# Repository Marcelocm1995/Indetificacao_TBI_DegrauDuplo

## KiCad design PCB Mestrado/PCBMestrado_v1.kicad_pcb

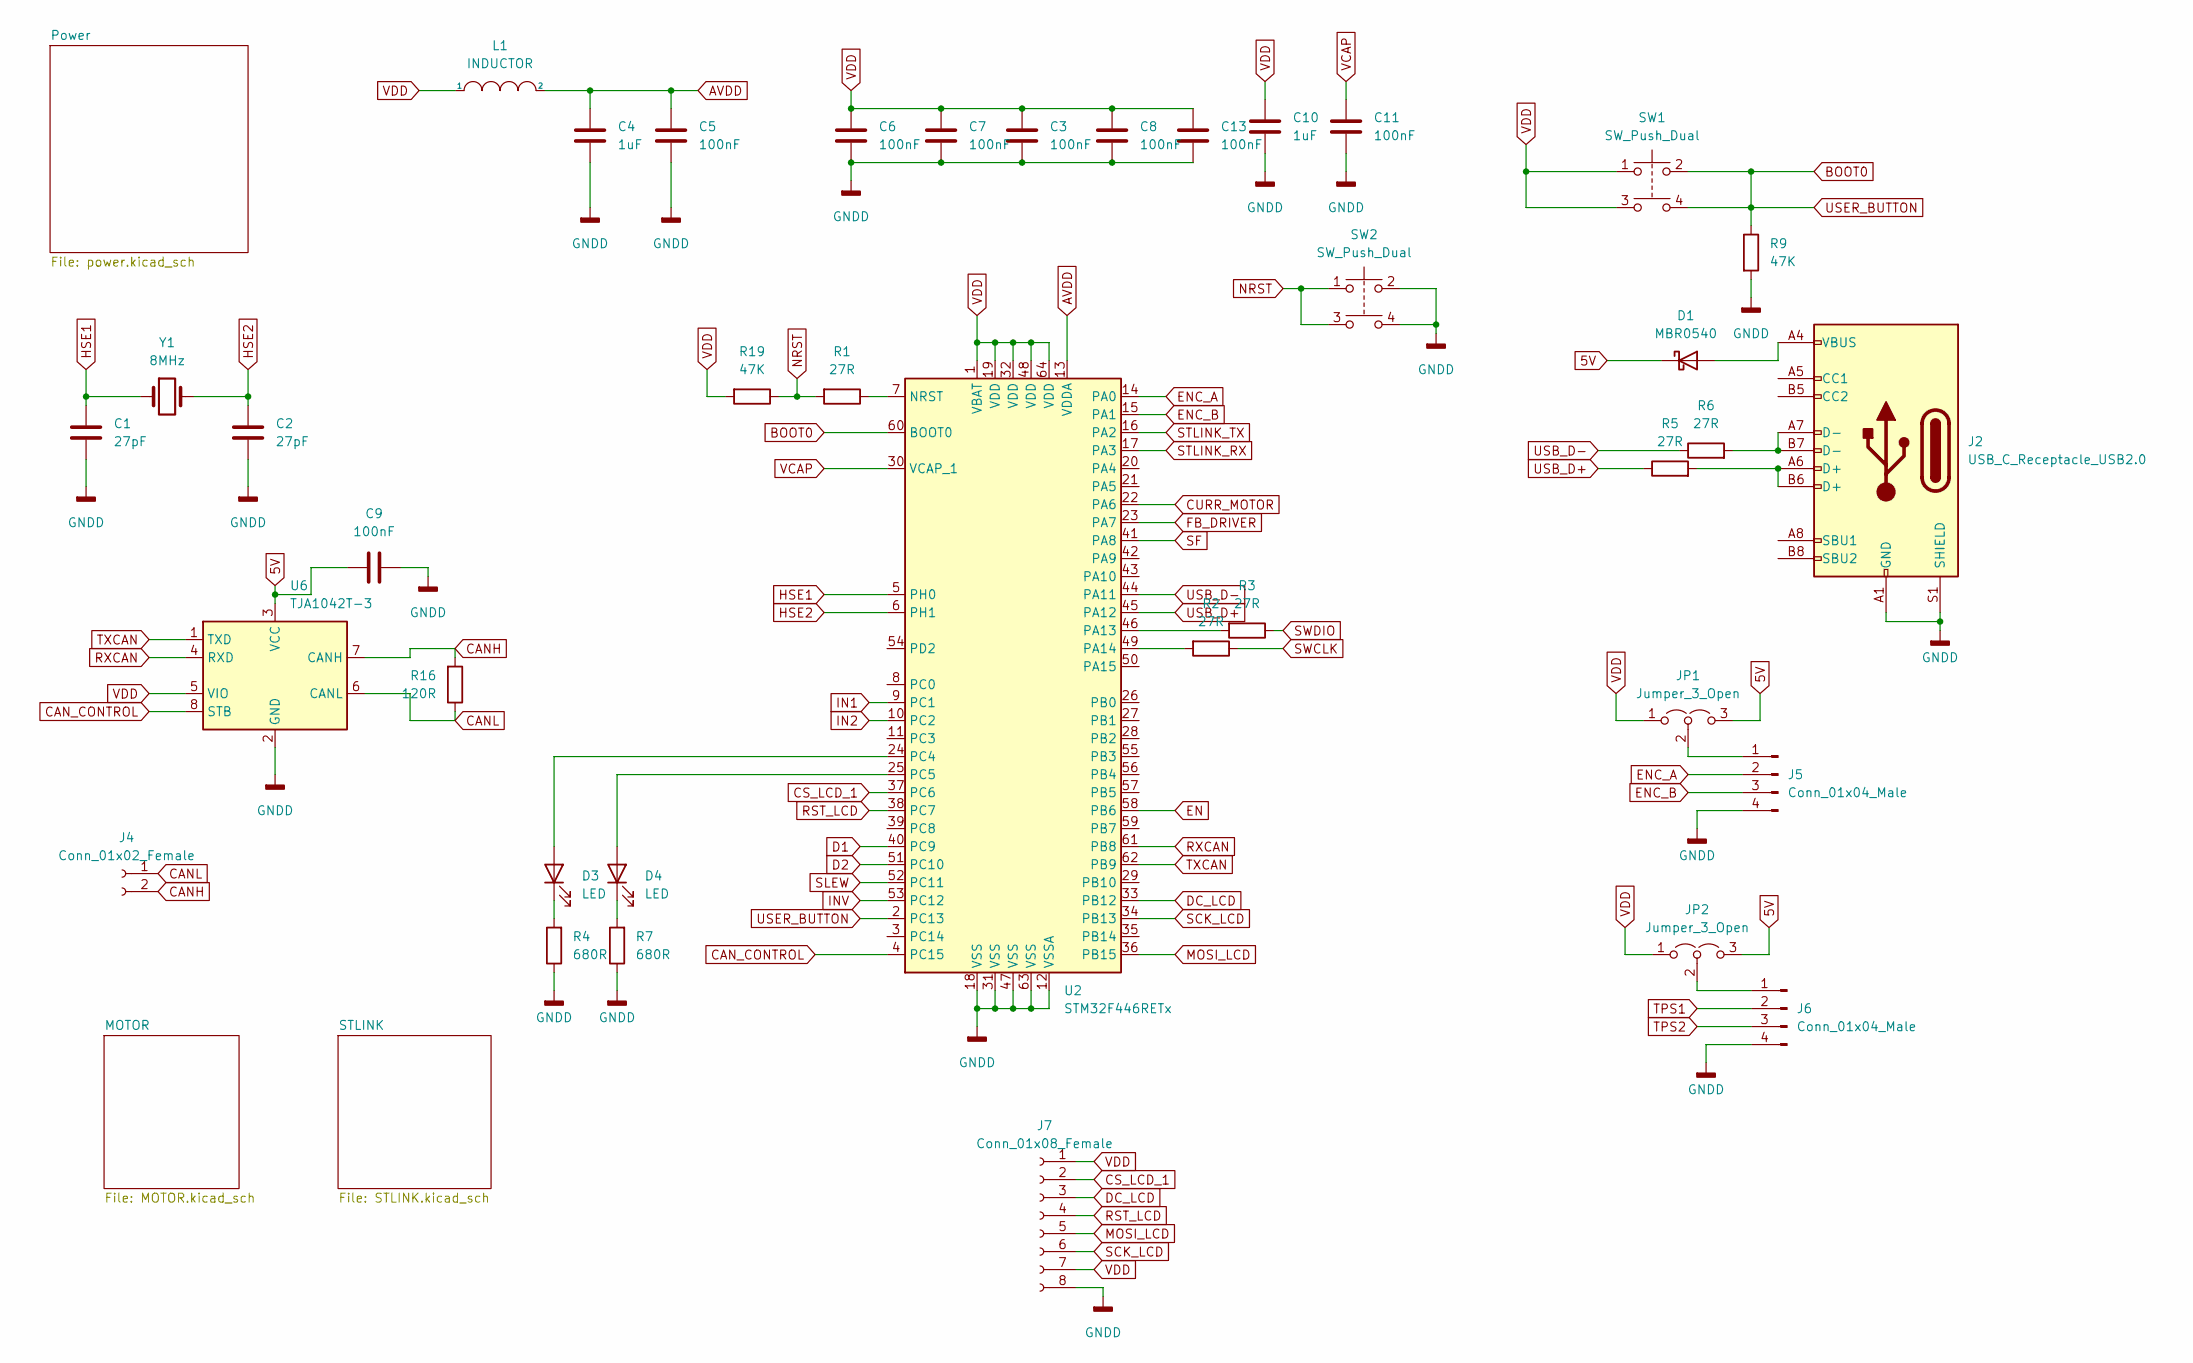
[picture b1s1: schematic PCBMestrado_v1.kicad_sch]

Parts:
C1, C2: 27pF; C_0603_1608Metric; LCSC Part C1653
C3, C5, C6, C7, C8, C9, C11, C13: 100nF; C_0603_1608Metric; LCSC Part C14663
C4, C10: 1uF; C_1206_3216Metric; LCSC Part C1848
D1: MBR0540; D_SOD-123; LCSC Part C699113
D3, D4: LED; LED_0603_1608Metric
J2: USB_C_Receptacle_USB2.0; USB_C_Receptacle_HRO_TYPE-C-31-M-12
J4: Conn_01x02_Female; PhoenixContact_MSTBA_2,5_2-G-5,08_1x02_P5.08mm_Horizontal
J5, J6: Conn_01x04_Male; JST_EH_B4B-EH-A_1x04_P2.50mm_Vertical
J7: Conn_01x08_Female; JST_EH_B8B-EH-A_1x08_P2.50mm_Vertical
JP1, JP2: Jumper_3_Open; SolderJumper-3_P2.0mm_Open_TrianglePad1.0x1.5mm
L1: INDUCTOR; L_0603_1608Metric; LCSC Part C2907080
R1, R2, R3: 27R; R_0603_1608Metric; LCSC Part C25819
R4, R7: 680R; R_0603_1608Metric; LCSC Part C25190
R5, R6: 27R; R_0603_1608Metric; LCSC Part C25190
R9, R19: 47K; R_0603_1608Metric; LCSC Part C25819
R16: 120R; R_0603_1608Metric
SW1, SW2: SW_Push_Dual; SW_SPST_TL3342
U2: STM32F446RETx; LQFP-64_10x10mm_P0.5mm
U6: TJA1042T-3; SOIC-8_3.9x4.9mm_P1.27mm
Y1: 8MHz; Crystal_SMD_3225-4Pin_3.2x2.5mm; LCSC Part C518154

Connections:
5V: C9.1, D1.1 (K), JP1.3 (B), JP2.3 (B), U6.3 (VCC); also elsewhere on the board
AVDD: C4.1, C5.1, L1.2, U2.13 (VDDA)
BOOT0: R9.1, SW1.2, SW1.4, U2.2 (PC13), U2.60 (BOOT0)
CANH: J4.2, R16.2, U6.7 (CANH)
CANL: J4.1, R16.1, U6.6 (CANL)
CAN_CONTROL: U2.4 (PC15), U6.8 (STB)
CS_LCD_1: J7.2, U2.37 (PC6)
CURR_MOTOR: U2.22 (PA6); also elsewhere on the board
D1: U2.40 (PC9); also elsewhere on the board
D2: U2.51 (PC10); also elsewhere on the board
DC_LCD: J7.3, U2.33 (PB12)
EN: U2.58 (PB6); also elsewhere on the board
ENC_A: J5.2, U2.14 (PA0)
ENC_B: J5.3, U2.15 (PA1)
FB_DRIVER: U2.23 (PA7); also elsewhere on the board
GNDD: C1.2, C2.2, C3.2, C4.2, C5.2, C6.2, C7.2, C8.2, C9.2, C10.2, C11.2, C13.2, J2.A1 (GND), J2.A12 (GND), J2.B1 (GND), J2.B12 (GND), J2.S1 (SHIELD), J5.4, J6.4, J7.8, R4.1, R7.1, R9.2, SW2.2, SW2.4, U2.12 (VSSA), U2.18 (VSS), U2.31 (VSS), U2.47 (VSS), U2.63 (VSS), U6.2 (GND); also elsewhere on the board
HSE1: C1.1, U2.5 (PH0), Y1.1
HSE2: C2.1, U2.6 (PH1), Y1.2
IN1: U2.9 (PC1); also elsewhere on the board
IN2: U2.10 (PC2); also elsewhere on the board
INV: U2.53 (PC12); also elsewhere on the board
MOSI_LCD: J7.5, U2.36 (PB15)
NRST: R1.2, R19.1, SW2.1, SW2.3; also elsewhere on the board
unnamed: D1.2 (A), J2.A4 (VBUS), J2.A9 (VBUS), J2.B4 (VBUS), J2.B9 (VBUS)
unnamed: D3.1 (K), R4.2
unnamed: D4.1 (K), R7.2
unnamed: J2.A6 (D+), J2.B6 (D+), R5.2
unnamed: J2.A7 (D-), J2.B7 (D-), R6.2
unnamed: J5.1, JP1.2 (C)
unnamed: J6.1, JP2.2 (C)
unnamed: R1.1, U2.7 (NRST)
unnamed: R2.2, U2.49 (PA14)
unnamed: R3.2, U2.46 (PA13)
unnamed: D3.2 (A), U2.24 (PC4)
unnamed: D4.2 (A), U2.25 (PC5)
RST_LCD: J7.4, U2.38 (PC7)
RXCAN: U2.61 (PB8), U6.4 (RXD)
SCK_LCD: J7.6, U2.34 (PB13)
SF: U2.41 (PA8); also elsewhere on the board
SLEW: U2.52 (PC11); also elsewhere on the board
STLINK_RX: U2.17 (PA3); also elsewhere on the board
STLINK_TX: U2.16 (PA2); also elsewhere on the board
SWCLK: R2.1; also elsewhere on the board
SWDIO: R3.1; also elsewhere on the board
TPS1: J6.2
TPS2: J6.3
TXCAN: U2.62 (PB9), U6.1 (TXD)
USB_D+: R5.1, U2.45 (PA12)
USB_D-: R6.1, U2.44 (PA11)
VCAP: C11.1, U2.30 (VCAP_1)
VDD: C3.1, C6.1, C7.1, C8.1, C10.1, C13.1, J7.1, J7.7, JP1.1 (A), JP2.1 (A), L1.1, R19.2, SW1.1, SW1.3, U2.1 (VBAT), U2.19 (VDD), U2.32 (VDD), U2.48 (VDD), U2.64 (VDD), U6.5 (VIO); also elsewhere on the board

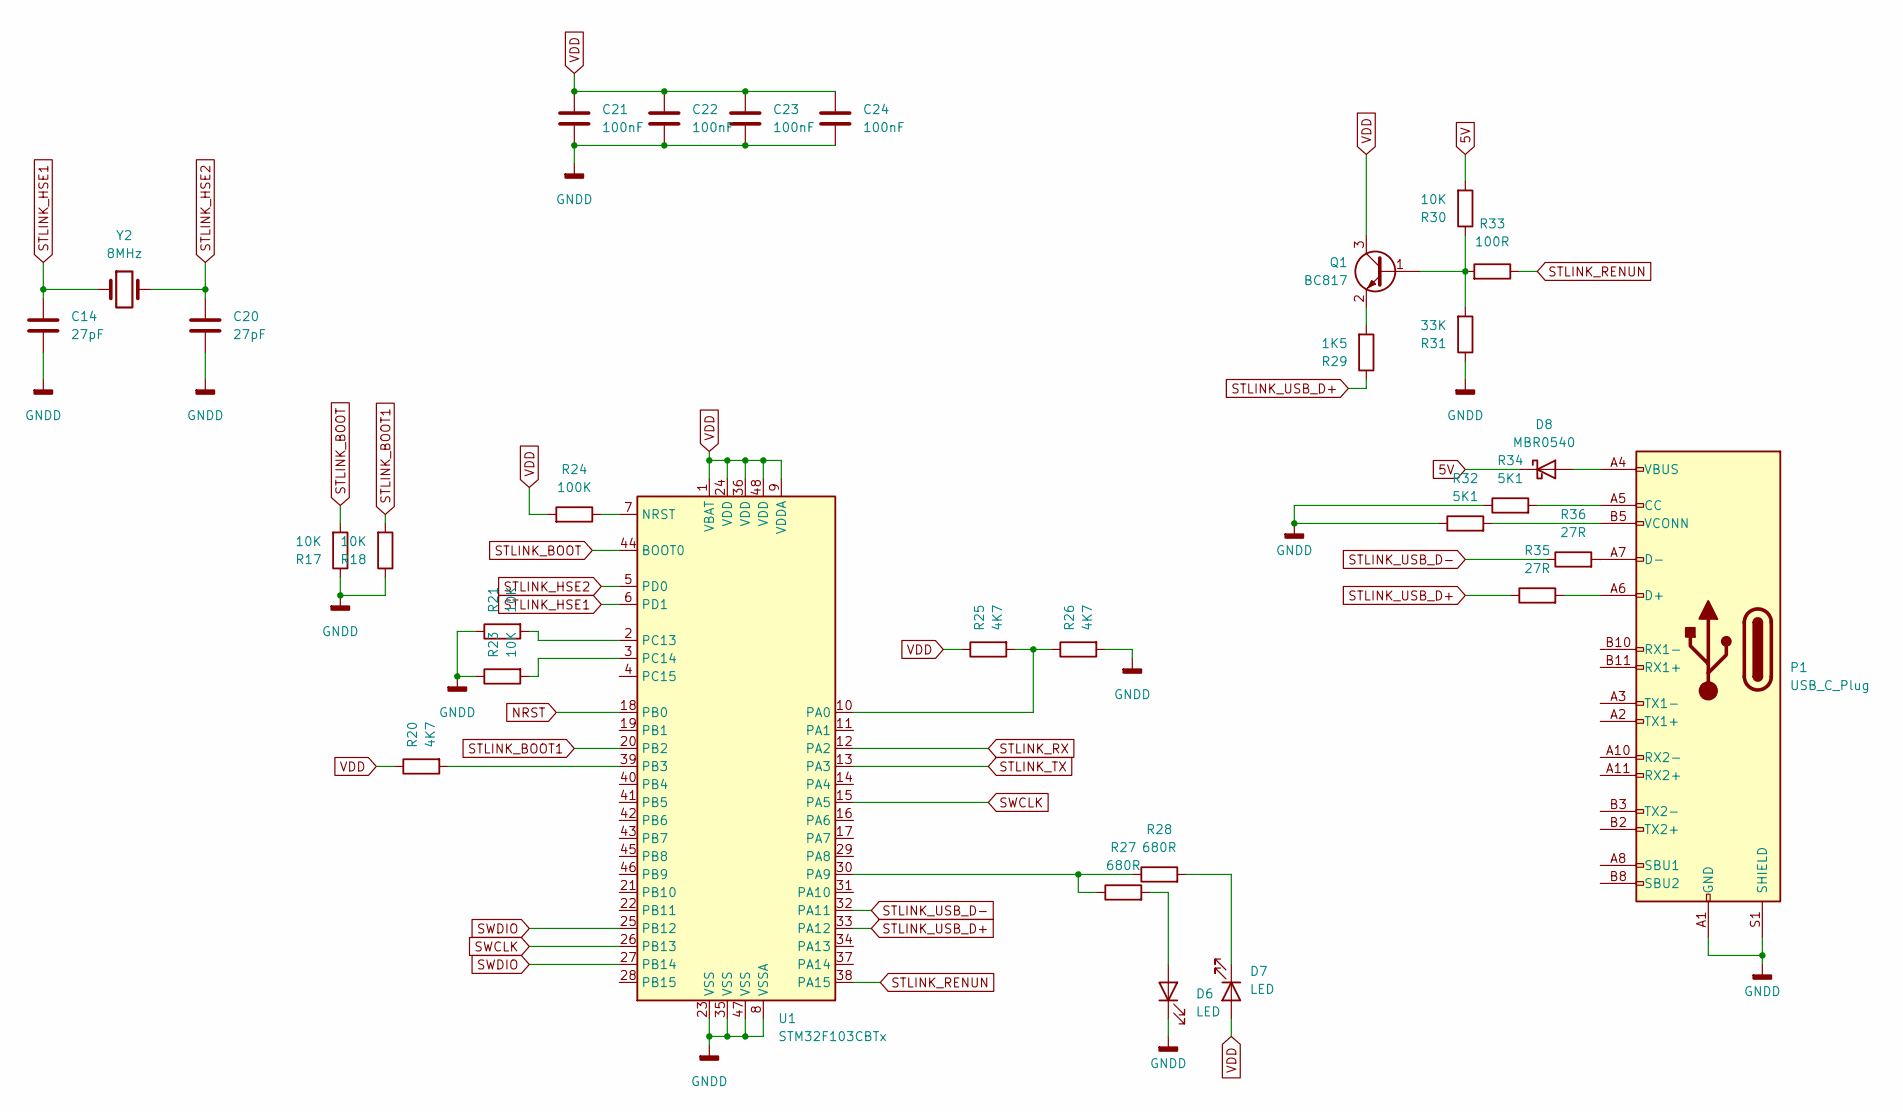
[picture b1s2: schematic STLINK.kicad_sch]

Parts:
C14, C20: 27pF; C_0603_1608Metric; LCSC Part C1653
C21, C22, C23, C24: 100nF; C_0603_1608Metric; LCSC Part C14663
D6, D7: LED; LED_0603_1608Metric
D8: MBR0540; D_SOD-123; LCSC Part C699113
P1: USB_C_Plug; USB_C_Receptacle_HRO_TYPE-C-31-M-12
Q1: BC817; SOT-23
R17, R18, R21, R23, R30: 10K; R_0603_1608Metric; LCSC Part C25190
R20, R25, R26: 4K7; R_0603_1608Metric; LCSC Part C25190
R24: 100K; R_0603_1608Metric; LCSC Part C25190
R27, R28: 680R; R_0603_1608Metric; LCSC Part C25190
R29: 1K5; R_0603_1608Metric; LCSC Part C25190
R31: 33K; R_0603_1608Metric; LCSC Part C25190
R32, R34: 5K1; R_0603_1608Metric; LCSC Part C25190
R33: 100R; R_0603_1608Metric; LCSC Part C25190
R35, R36: 27R; R_0603_1608Metric; LCSC Part C25190
U1: STM32F103CBTx; LQFP-48_7x7mm_P0.5mm
Y2: 8MHz; Crystal_SMD_3225-4Pin_3.2x2.5mm; LCSC Part C518154

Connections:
5V: D8.1 (K), R30.2; also elsewhere on the board
GNDD: C14.2, C20.2, C21.2, C22.2, C23.2, C24.2, D6.1 (K), P1.A1 (GND), P1.A12 (GND), P1.B1 (GND), P1.B12 (GND), P1.S1 (SHIELD), R17.1, R18.1, R21.1, R23.1, R26.2, R31.1, R32.1, R34.1, U1.8 (VSSA), U1.23 (VSS), U1.35 (VSS), U1.47 (VSS); also elsewhere on the board
NRST: U1.18 (PB0); also elsewhere on the board
unnamed: D6.2 (A), R27.2
unnamed: D7.1 (K), R28.2
unnamed: D8.2 (A), P1.A4 (VBUS), P1.A9 (VBUS), P1.B4 (VBUS), P1.B9 (VBUS)
unnamed: P1.A5 (CC), R34.2
unnamed: P1.A6 (D+), R35.2
unnamed: P1.A7 (D-), R36.2
unnamed: P1.B5 (VCONN), R32.2
unnamed: Q1.1 (B), R30.1, R31.2, R33.2
unnamed: Q1.2 (E), R29.2
unnamed: R20.2, U1.39 (PB3)
unnamed: R21.2, U1.2 (PC13)
unnamed: R23.2, U1.3 (PC14)
unnamed: R24.1, U1.7 (NRST)
unnamed: R25.2, R26.1, U1.10 (PA0)
unnamed: R27.1, R28.1, U1.30 (PA9)
STLINK_BOOT: R17.2, U1.44 (BOOT0)
STLINK_BOOT1: R18.2, U1.20 (PB2)
STLINK_HSE1: C14.1, U1.6 (PD1), Y2.1
STLINK_HSE2: C20.1, U1.5 (PD0), Y2.2
STLINK_RENUN: R33.1, U1.38 (PA15)
STLINK_RX: U1.12 (PA2); also elsewhere on the board
STLINK_TX: U1.13 (PA3); also elsewhere on the board
STLINK_USB_D+: R29.1, R35.1, U1.33 (PA12)
STLINK_USB_D-: R36.1, U1.32 (PA11)
SWCLK: U1.15 (PA5), U1.26 (PB13); also elsewhere on the board
SWDIO: U1.25 (PB12), U1.27 (PB14); also elsewhere on the board
VDD: C21.1, C22.1, C23.1, C24.1, D7.2 (A), Q1.3 (C), R20.1, R24.2, R25.1, U1.1 (VBAT), U1.9 (VDDA), U1.24 (VDD), U1.36 (VDD), U1.48 (VDD); also elsewhere on the board

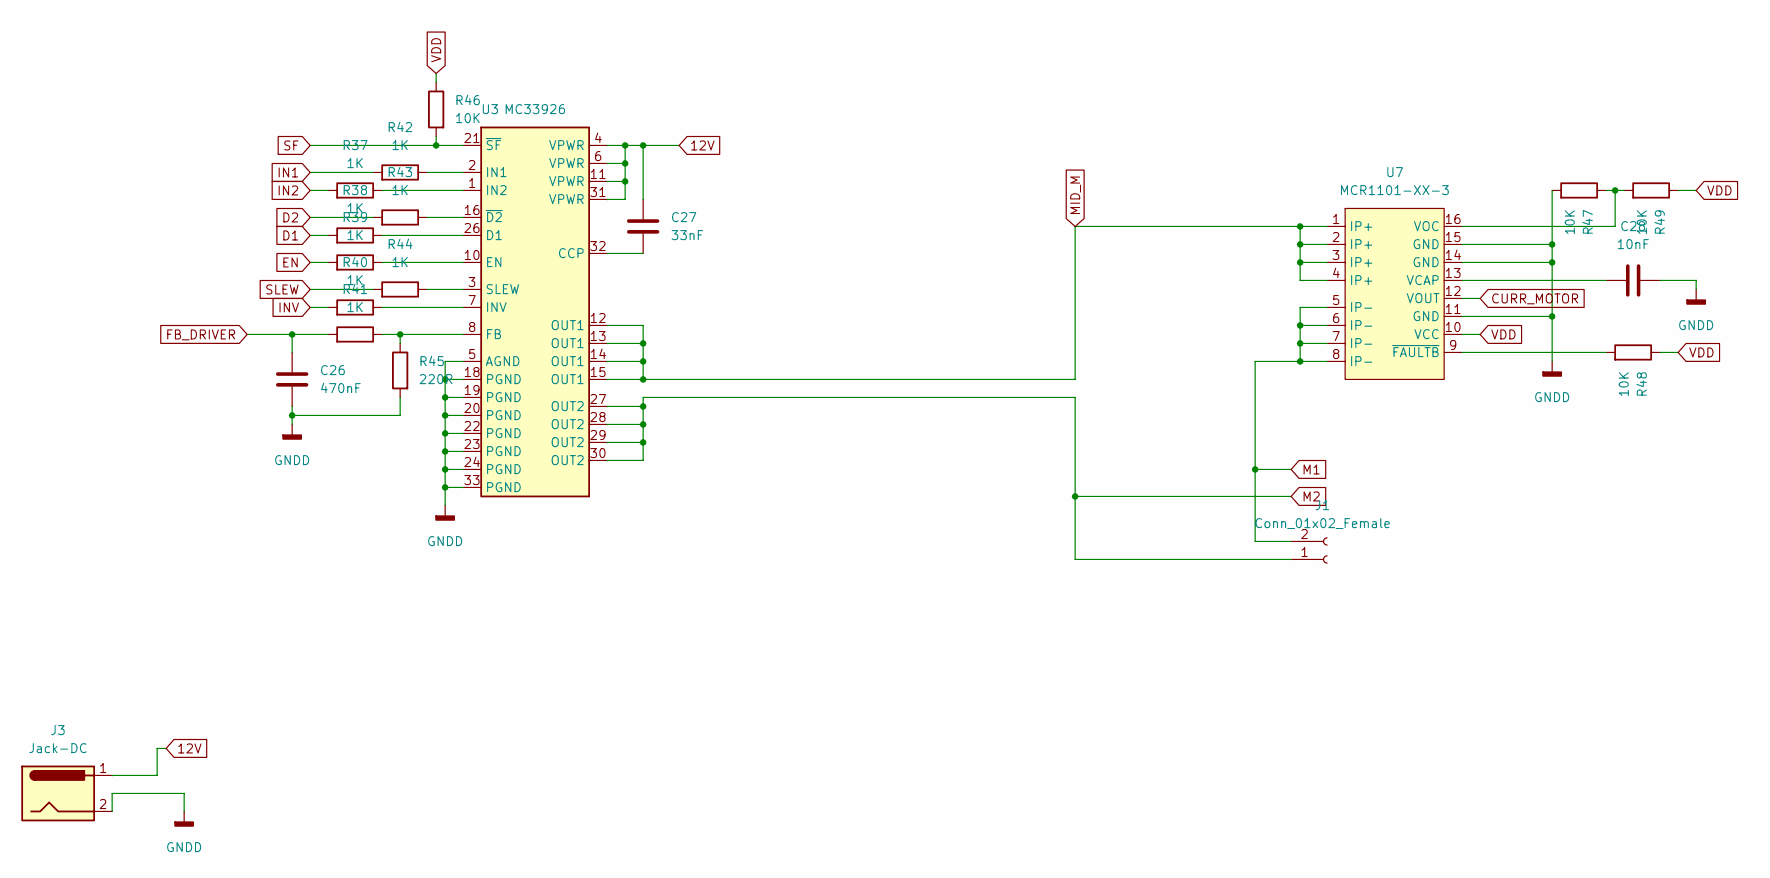
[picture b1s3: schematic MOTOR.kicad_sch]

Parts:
C26: 470nF; C_0603_1608Metric; LCSC Part C1848
C27: 33nF; C_1206_3216Metric; LCSC Part C1848
C28: 10nF; C_0603_1608Metric; LCSC Part C1848
J1: Conn_01x02_Female; PhoenixContact_MSTBA_2,5_2-G-5,08_1x02_P5.08mm_Horizontal
J3: Jack-DC; BarrelJack_GCT_DCJ200-10-A_Horizontal
R37, R38, R39, R40, R41, R42, R43, R44: 1K; R_0603_1608Metric
R45: 220R; R_0603_1608Metric
R46, R47, R48, R49: 10K; R_0603_1608Metric
U3: MC33926; QPFN32 8X8 0.8MM
U7: MCR1101-XX-3; SOIC-16W_5.3x10.2mm_P1.27mm

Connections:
12V: C27.1, J3.1, U3.4 (VPWR), U3.6 (VPWR), U3.11 (VPWR), U3.31 (VPWR); also elsewhere on the board
CURR_MOTOR: U7.12 (VOUT); also elsewhere on the board
D1: R38.2; also elsewhere on the board
D2: R43.2; also elsewhere on the board
EN: R39.2; also elsewhere on the board
FB_DRIVER: C26.1, R41.2; also elsewhere on the board
GNDD: C26.2, C28.2, J3.2, R45.2, R47.2, U3.5 (AGND), U3.18 (PGND), U3.19 (PGND), U3.20 (PGND), U3.22 (PGND), U3.23 (PGND), U3.24 (PGND), U3.33 (PGND), U7.11 (GND), U7.14 (GND), U7.15 (GND); also elsewhere on the board
IN1: R42.2; also elsewhere on the board
IN2: R37.2; also elsewhere on the board
INV: R40.2; also elsewhere on the board
M1: J1.2, U7.5 (IP-), U7.6 (IP-), U7.7 (IP-), U7.8 (IP-)
M2: J1.1, U3.27 (OUT2), U3.28 (OUT2), U3.29 (OUT2), U3.30 (OUT2)
MID_M: U3.12 (OUT1), U3.13 (OUT1), U3.14 (OUT1), U3.15 (OUT1), U7.1 (IP+), U7.2 (IP+), U7.3 (IP+), U7.4 (IP+)
unnamed: C27.2, U3.32 (CCP)
unnamed: C28.1, U7.13 (VCAP)
unnamed: R37.1, U3.1 (IN2)
unnamed: R38.1, U3.26 (D1)
unnamed: R39.1, U3.10 (EN)
unnamed: R40.1, U3.7 (INV)
unnamed: R41.1, R45.1, U3.8 (FB)
unnamed: R42.1, U3.2 (IN1)
unnamed: R43.1, U3.16 (~D2)
unnamed: R44.1, U3.3 (SLEW)
unnamed: R47.1, R49.2, U7.16 (VOC)
unnamed: R48.2, U7.9 (~FAULTB)
SF: R46.2, U3.21 (~SF); also elsewhere on the board
SLEW: R44.2; also elsewhere on the board
VDD: R46.1, R48.1, R49.1, U7.10 (VCC); also elsewhere on the board

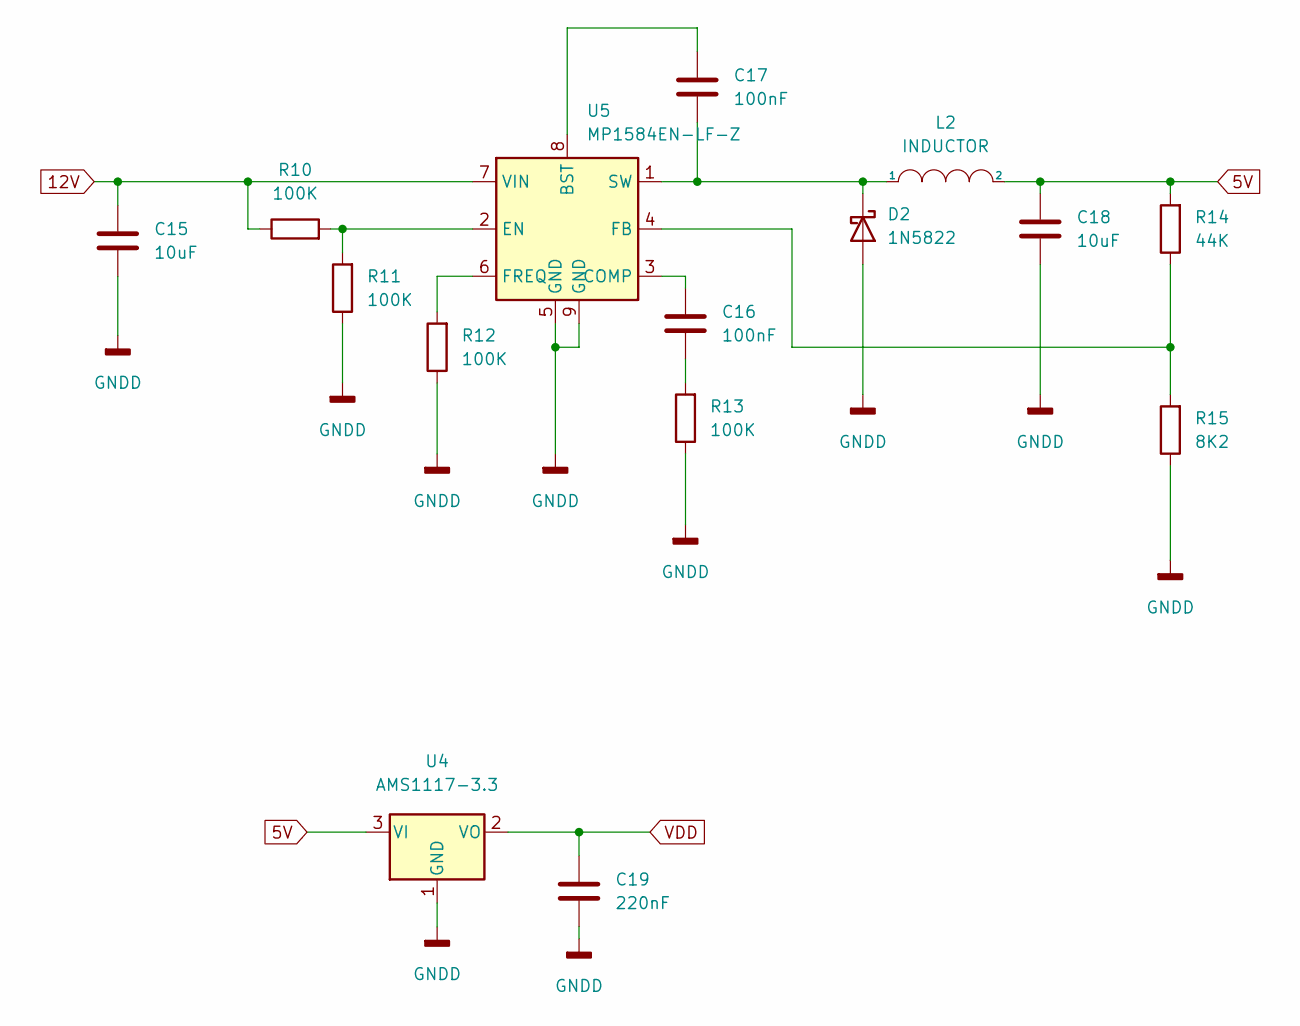
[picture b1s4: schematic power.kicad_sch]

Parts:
C15, C18: 10uF; C_1206_3216Metric; LCSC Part C13585
C16, C17: 100nF; C_0603_1608Metric; LCSC Part C14663
C19: 220nF; C_0603_1608Metric; LCSC Part C21120
D2: 1N5822; D_SMA; LCSC Part C8678
L2: INDUCTOR; L_7.3x7.3_H3.5; LCSC Part C167220
R10, R11, R12, R13: 100K; R_0603_1608Metric; LCSC Part C25803
R14: 44K; R_0603_1608Metric; LCSC Part C309448
R15: 8K2; R_0603_1608Metric; LCSC Part C25981
U4: AMS1117-3.3; SOT-223-3_TabPin2; LCSC Part C6186
U5: MP1584EN-LF-Z; SOIC-8-1EP_3.9x4.9mm_P1.27mm_EP2.62x3.51mm; LCSC Part C15051

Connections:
5V: C18.1, L2.2, R14.2, U4.3 (VI); also elsewhere on the board
12V: C15.1, R10.1, U5.7 (VIN); also elsewhere on the board
GNDD: C15.2, C18.2, C19.2, D2.2 (A), R11.1, R12.1, R13.1, R15.1, U4.1 (GND), U5.5 (GND), U5.9 (GND); also elsewhere on the board
unnamed: C16.1, U5.3 (COMP)
unnamed: C16.2, R13.2
unnamed: C17.1, U5.8 (BST)
unnamed: C17.2, D2.1 (K), L2.1, U5.1 (SW)
unnamed: R10.2, R11.2, U5.2 (EN)
unnamed: R12.2, U5.6 (FREQ)
unnamed: R14.1, R15.2, U5.4 (FB)
VDD: C19.1, U4.2 (VO); also elsewhere on the board

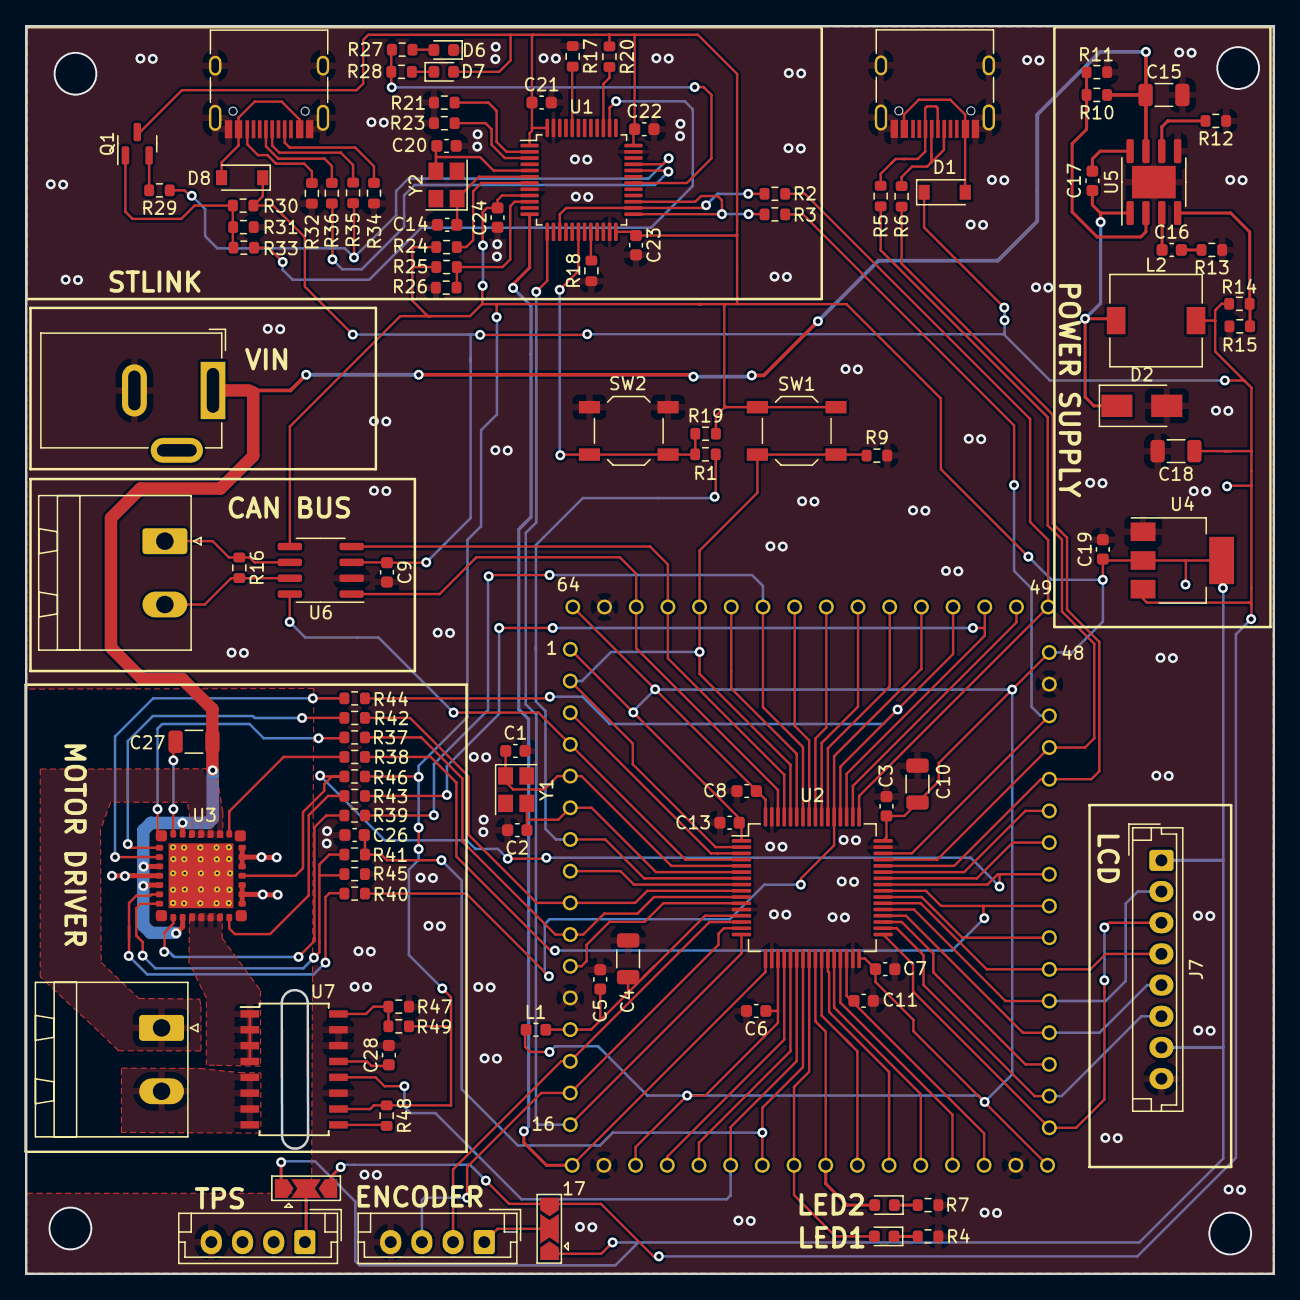
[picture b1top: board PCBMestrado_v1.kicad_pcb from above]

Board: 2 copper layers, 100.0 x 100.0 mm, 104 parts (0 on the bottom side), 94 nets.

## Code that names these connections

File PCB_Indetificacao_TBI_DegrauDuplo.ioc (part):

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Mcu.Name=STM32F446R(C-E)Tx
Mcu.Package=LQFP64
Mcu.UserName=STM32F446RETx
PA0-WKUP.Signal=S_TIM2_CH1_ETR
PA1.Signal=S_TIM2_CH2
PA11.Signal=USB_OTG_FS_DM
PA12.Signal=USB_OTG_FS_DP
PA13.GPIOParameters=GPIO_Label
PA13.GPIO_Label=TMS
PA13.Mode=Serial_Wire
PA13.Signal=SYS_JTMS-SWDIO
PA14.GPIOParameters=GPIO_Label
PA14.GPIO_Label=TCK
PA14.Mode=Serial_Wire
PA14.Signal=SYS_JTCK-SWCLK
PA2.GPIOParameters=GPIO_Label
PA2.GPIO_Label=USART_TX
PA2.Mode=Asynchronous
PA2.Signal=USART2_TX
PA3.GPIOParameters=GPIO_Label
PA3.GPIO_Label=USART_RX
PA3.Mode=Asynchronous
PA3.Signal=USART2_RX
PA6.GPIOParameters=GPIO_Label
PA6.GPIO_Label=CURR_MOTOR
PA6.Signal=ADCx_IN6
PA7.GPIOParameters=GPIO_Label
PA7.GPIO_Label=FB_DRIVER
PA7.Signal=ADCx_IN7
PA8.GPIOParameters=GPIO_Label
PA8.GPIO_Label=SF
PA8.Signal=GPIO_Input
PB12.GPIOParameters=GPIO_Label
PB12.GPIO_Label=DC_LCD
PB12.Signal=GPIO_Output
PB13.Mode=TX_Only_Simplex_Unidirect_Master
PB13.Signal=SPI2_SCK
PB14.Signal=SPI2_MISO
PB15.Mode=TX_Only_Simplex_Unidirect_Master
PB15.Signal=SPI2_MOSI
PB6.GPIOParameters=GPIO_Label
PB6.GPIO_Label=EN
PB6.Signal=S_TIM4_CH1
PB8.Mode=CAN_Activate
PB8.Signal=CAN1_RX
PB9.Mode=CAN_Activate
PB9.Signal=CAN1_TX
PC10.GPIOParameters=GPIO_Label
PC10.GPIO_Label=D2
PC10.Signal=GPIO_Output
PC11.GPIOParameters=GPIO_Label
PC11.GPIO_Label=SLEW
PC11.Signal=GPIO_Output
PC12.GPIOParameters=GPIO_Label
PC12.GPIO_Label=INV
PC12.Signal=GPIO_Output
PC13.GPIOParameters=GPIO_Label,GPIO_ModeDefaultEXTI
PC13.GPIO_Label=B1 [Blue PushButton]
PC13.GPIO_ModeDefaultEXTI=GPIO_MODE_IT_FALLING
PC13.Signal=GPXTI13
PC15-OSC32_OUT.GPIOParameters=GPIO_PuPd,GPIO_Label,GPIO_ModeDefaultOutputPP
PC15-OSC32_OUT.GPIO_Label=CAN_CONTROL
PC15-OSC32_OUT.GPIO_ModeDefaultOutputPP=GPIO_MODE_OUTPUT_OD
PC15-OSC32_OUT.GPIO_PuPd=GPIO_NOPULL
PC15-OSC32_OUT.Signal=GPIO_Output
PC4.GPIOParameters=GPIO_Label
PC4.GPIO_Label=LED1
PC4.Signal=GPIO_Output
PC5.GPIOParameters=GPIO_Label
PC5.GPIO_Label=LED2
PC5.Signal=GPIO_Output
PC6.GPIOParameters=GPIO_Label
PC6.GPIO_Label=CS_LCD
PC6.Signal=GPIO_Output
PC7.GPIOParameters=GPIO_Label
PC7.GPIO_Label=RST_LCD
PC7.Signal=GPIO_Output
PC9.GPIOParameters=GPIO_Label
PC9.GPIO_Label=D1
PC9.Signal=GPIO_Output
PH0-OSC_IN.Mode=HSE-External-Oscillator
PH0-OSC_IN.Signal=RCC_OSC_IN
PH1-OSC_OUT.Mode=HSE-External-Oscillator
PH1-OSC_OUT.Signal=RCC_OSC_OUT
RCC.HSE_VALUE=8000000
RCC.SYSCLKFreq_VALUE=180000000
RCC.SYSCLKSource=RCC_SYSCLKSOURCE_PLLCLK
board=NUCLEO-F446RE
boardIOC=true

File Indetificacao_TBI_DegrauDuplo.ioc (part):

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Mcu.Name=STM32F446R(C-E)Tx
Mcu.Package=LQFP64
Mcu.UserName=STM32F446RETx
PA0-WKUP.Signal=S_TIM2_CH1_ETR
PA1.Signal=S_TIM2_CH2
PA13.GPIOParameters=GPIO_Label
PA13.GPIO_Label=TMS
PA13.Mode=Serial_Wire
PA13.Signal=SYS_JTMS-SWDIO
PA14.GPIOParameters=GPIO_Label
PA14.GPIO_Label=TCK
PA14.Mode=Serial_Wire
PA14.Signal=SYS_JTCK-SWCLK
PA2.GPIOParameters=GPIO_Label
PA2.GPIO_Label=USART_TX
PA2.Mode=Asynchronous
PA2.Signal=USART2_TX
PA3.GPIOParameters=GPIO_Label
PA3.GPIO_Label=USART_RX
PA3.Mode=Asynchronous
PA3.Signal=USART2_RX
PA4.Signal=ADCx_IN4
PA5.GPIOParameters=GPIO_Label
PA5.GPIO_Label=LD2 [Green Led]
PA5.Signal=GPIO_Output
PA6.GPIOParameters=GPIO_Label
PA6.GPIO_Label=LD1
PA6.Signal=GPIO_Output
PA8.GPIOParameters=GPIO_Label
PA8.GPIO_Label=IN1_H
PA8.Signal=GPIO_Output
PA9.Signal=S_TIM1_CH2
PB10.GPIOParameters=GPIO_Label
PB10.GPIO_Label=IN2_H
PB10.Signal=GPIO_Output
PB12.GPIOParameters=GPIO_Label
PB12.GPIO_Label=DC_LCD
PB12.Signal=GPIO_Output
PB13.Mode=TX_Only_Simplex_Unidirect_Master
PB13.Signal=SPI2_SCK
PB14.Signal=SPI2_MISO
PB15.Mode=TX_Only_Simplex_Unidirect_Master
PB15.Signal=SPI2_MOSI
PB3.GPIOParameters=GPIO_Label
PB3.GPIO_Label=SWO
PB3.Signal=SYS_JTDO-SWO
PB6.Signal=S_TIM4_CH1
PC0.Signal=ADCx_IN10
PC13.GPIOParameters=GPIO_Label,GPIO_ModeDefaultEXTI
PC13.GPIO_Label=B1 [Blue PushButton]
PC13.GPIO_ModeDefaultEXTI=GPIO_MODE_IT_FALLING
PC13.Signal=GPXTI13
PC14-OSC32_IN.Mode=LSE-External-Oscillator
PC14-OSC32_IN.Signal=RCC_OSC32_IN
PC15-OSC32_OUT.Mode=LSE-External-Oscillator
PC15-OSC32_OUT.Signal=RCC_OSC32_OUT
PC6.GPIOParameters=GPIO_Label
PC6.GPIO_Label=CS_LCD
PC6.Signal=GPIO_Output
PC7.GPIOParameters=GPIO_Label
PC7.GPIO_Label=RST_LCD
PC7.Signal=GPIO_Output
PH0-OSC_IN.Mode=HSE-External-Oscillator
PH0-OSC_IN.Signal=RCC_OSC_IN
PH1-OSC_OUT.Mode=HSE-External-Oscillator
PH1-OSC_OUT.Signal=RCC_OSC_OUT
RCC.HSE_VALUE=8000000
RCC.SYSCLKFreq_VALUE=144000000
RCC.SYSCLKSource=RCC_SYSCLKSOURCE_PLLCLK
board=NUCLEO-F446RE
boardIOC=true

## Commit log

2022-08-07 building
2022-08-17 pcb building
2022-08-24 build
2022-08-28 ADC speed improved
